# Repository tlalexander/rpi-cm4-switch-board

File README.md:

# RPi CM4 - Gigabit switch prototyping board

A raspberry pi cm4 board with integrated gigabit switch.

Two CM4s and three RJ45 Jacks each connected to a [Microchip KSZ9567](https://www.microchip.com/wwwproducts/en/KSZ9567#datasheet-toggle)

In the future I will make a board with four CM4 modules and one RJ45 on the
switch, but for now I am making this so I can test the switch on its own.

However this also makes for an interesting board in its own right, as two
wifi CM4 modules could make this an interesting router board.

## About

This project is maintained by [Taylor Alexander](http://tlalexander.com).

The Raspberry Pi CM4 is a product of [Raspberry Pi (Trading) Limited](https://www.raspberrypi.org/about/).

This Raspberry Pi CM4 switch board was forked from
[Alexander Rau's](https://rpi.loonix.ca) rpi-cm4-LiM-board:
https://github.com/l00nix/rpi-cm4-LiM-board

Alexander Rau forked the rpi-cm4-LiM-board board design from [Shawn Hymel](https://github.com/ShawnHymel/rpi-cm4-base-carrier).
Shawn has a two part youtube series on how to design a CM4 Carrier Board.

- [Part 1 - How to Make a Raspberry Pi Compute Module 4 Carrier Board in KiCad](https://www.youtube.com/watch?v=ypcPJC_umPQ)
- [Part 2 - How to Make a Raspberry Pi Compute Module 4 Carrier Board in KiCad](https://www.youtube.com/watch?v=ge6gYIENo8Q&t)

## License

Schematic and PCB layout files are licensed under the [CC BY 4.0](https://creativecommons.org/licenses/by/2.0/) license.

Individual components and footprints found in the CM4IO library are licensed as
per the Design Files license found [here](https://datasheets.raspberrypi.org/license.html).

THE DESIGN IS PROVIDED "AS IS" AND THE AUTHOR DISCLAIMS ALL WARRANTIES WITH
REGARD TO THIS DESIGN INCLUDING ALL IMPLIED WARRANTIES OF MERCHANTABILITY AND
FITNESS. IN NO EVENT SHALL THE AUTHOR BE LIABLE FOR ANY SPECIAL, DIRECT,
INDIRECT, OR CONSEQUENTIAL DAMAGES OR ANY DAMAGES WHATSOEVER RESULTING FROM
LOSS OF USE, DATA OR PROFITS, WHETHER IN AN ACTION OF CONTRACT, NEGLIGENCE
OR OTHER TORTIOUS ACTION, ARISING OUT OF OR IN CONNECTION WITH THE USE OR
PERFORMANCE OF THIS DESIGN.

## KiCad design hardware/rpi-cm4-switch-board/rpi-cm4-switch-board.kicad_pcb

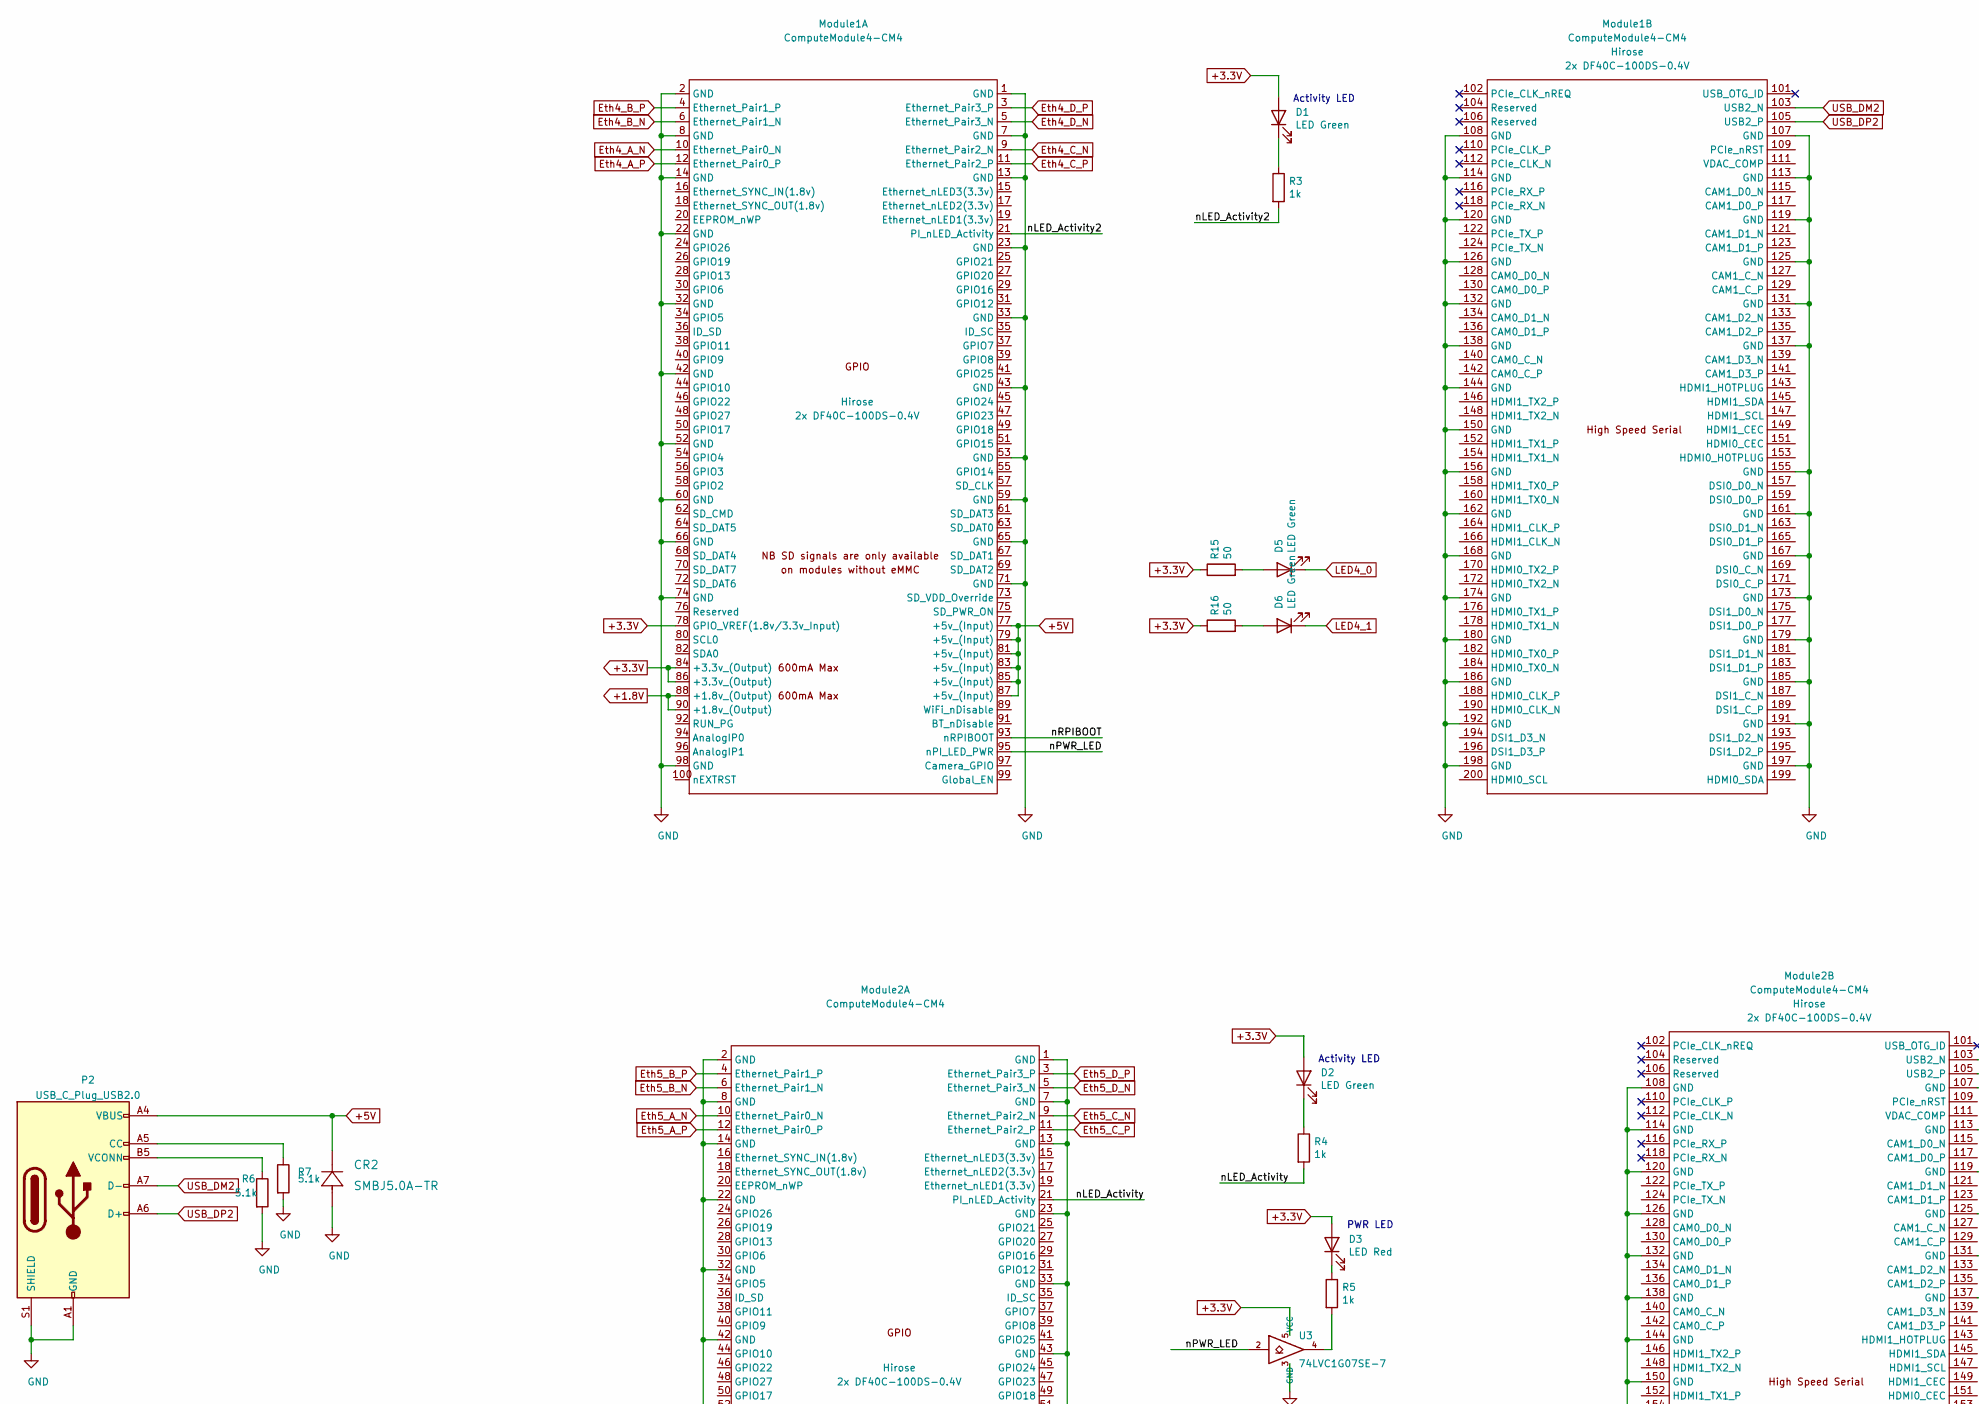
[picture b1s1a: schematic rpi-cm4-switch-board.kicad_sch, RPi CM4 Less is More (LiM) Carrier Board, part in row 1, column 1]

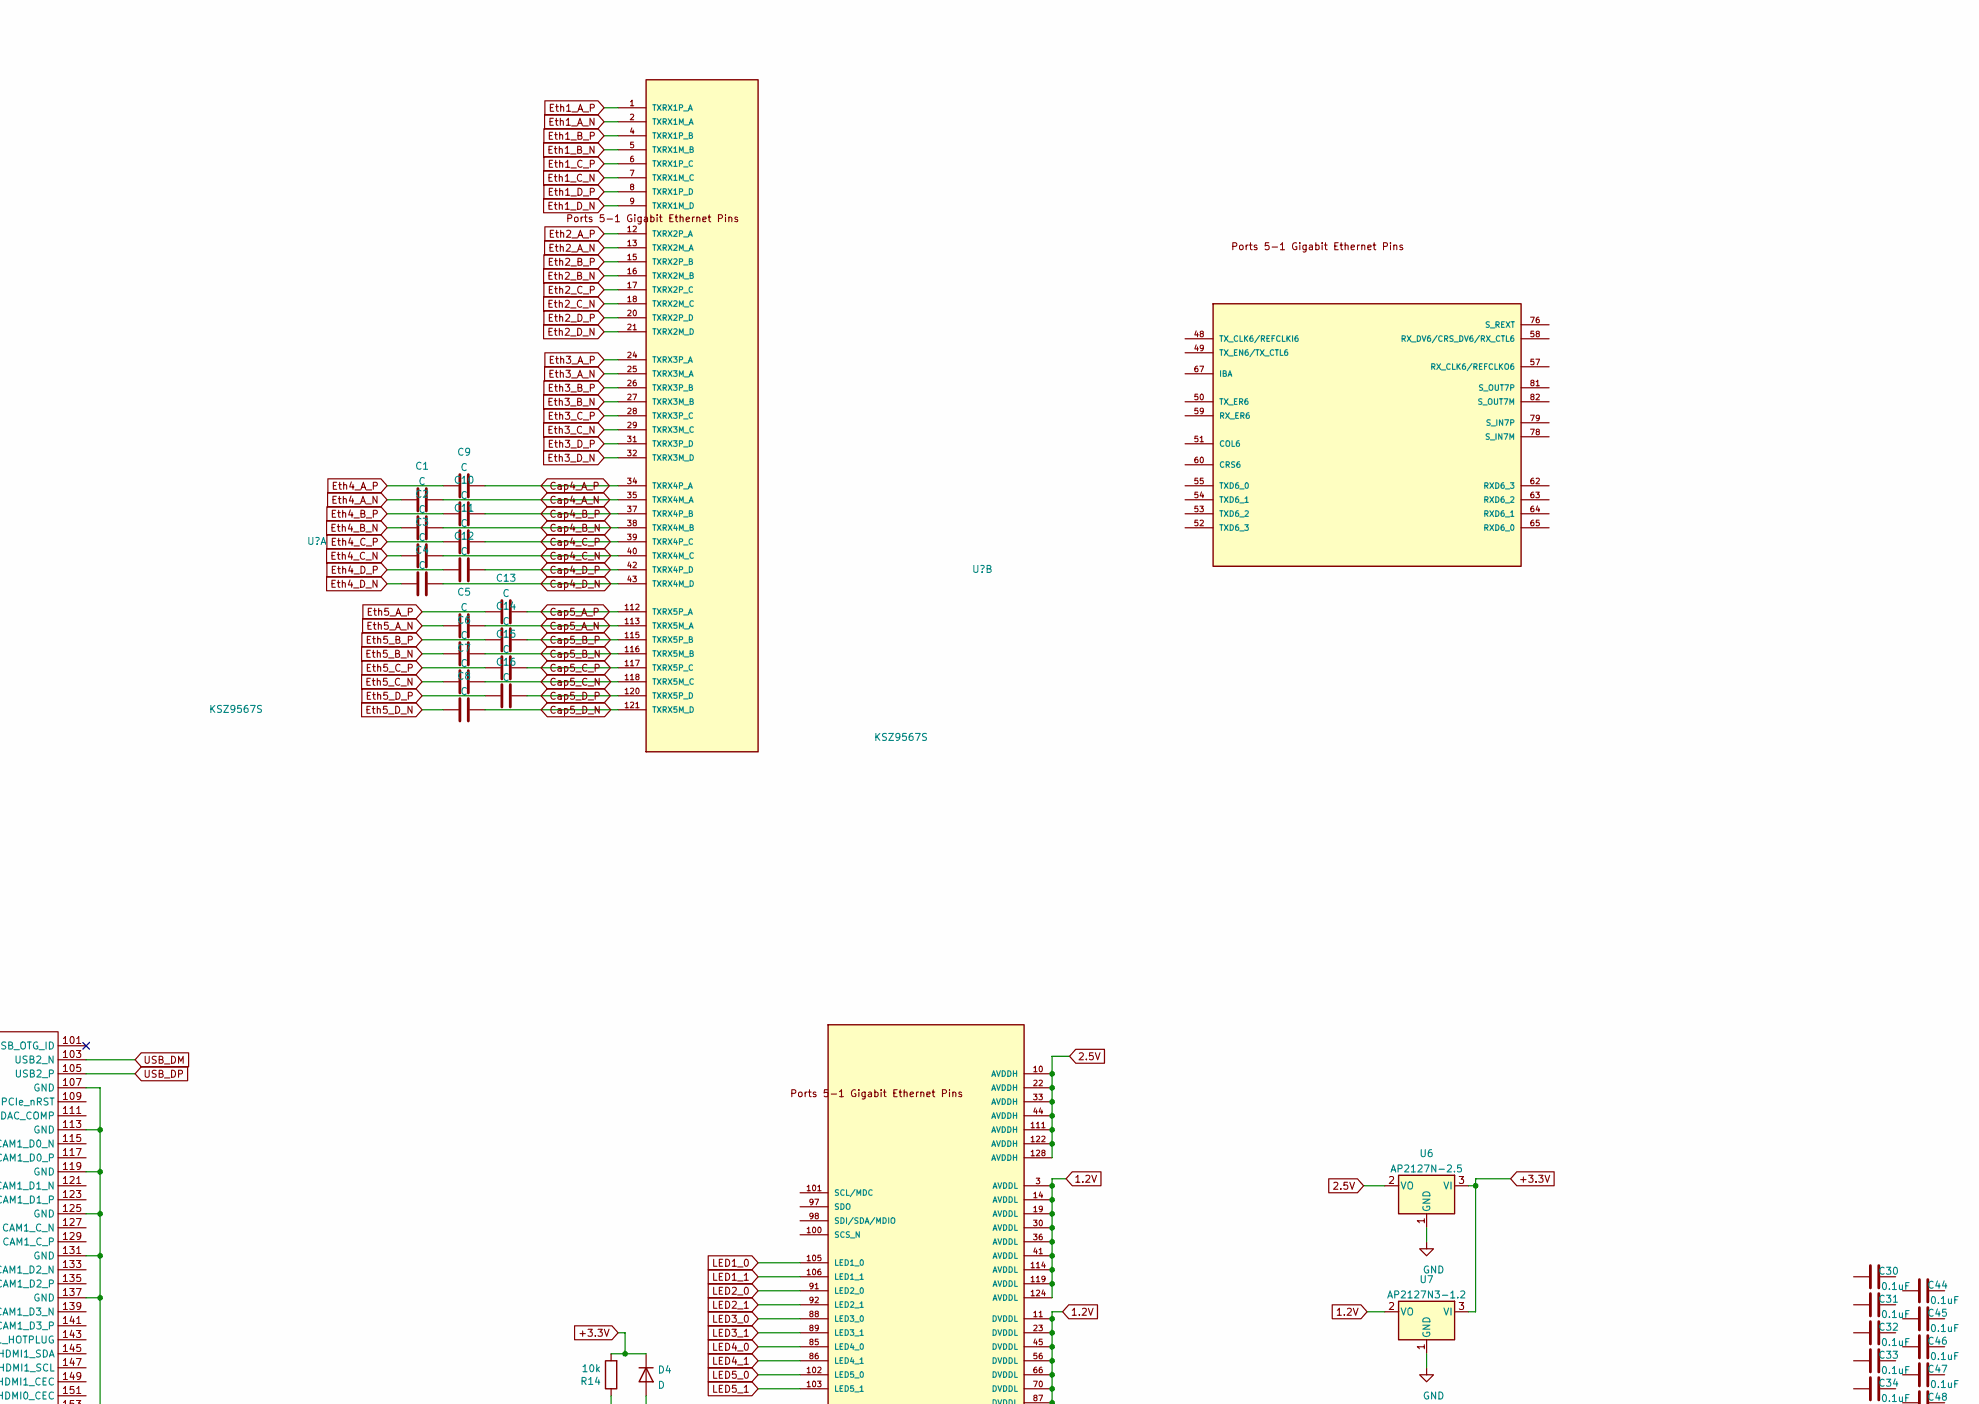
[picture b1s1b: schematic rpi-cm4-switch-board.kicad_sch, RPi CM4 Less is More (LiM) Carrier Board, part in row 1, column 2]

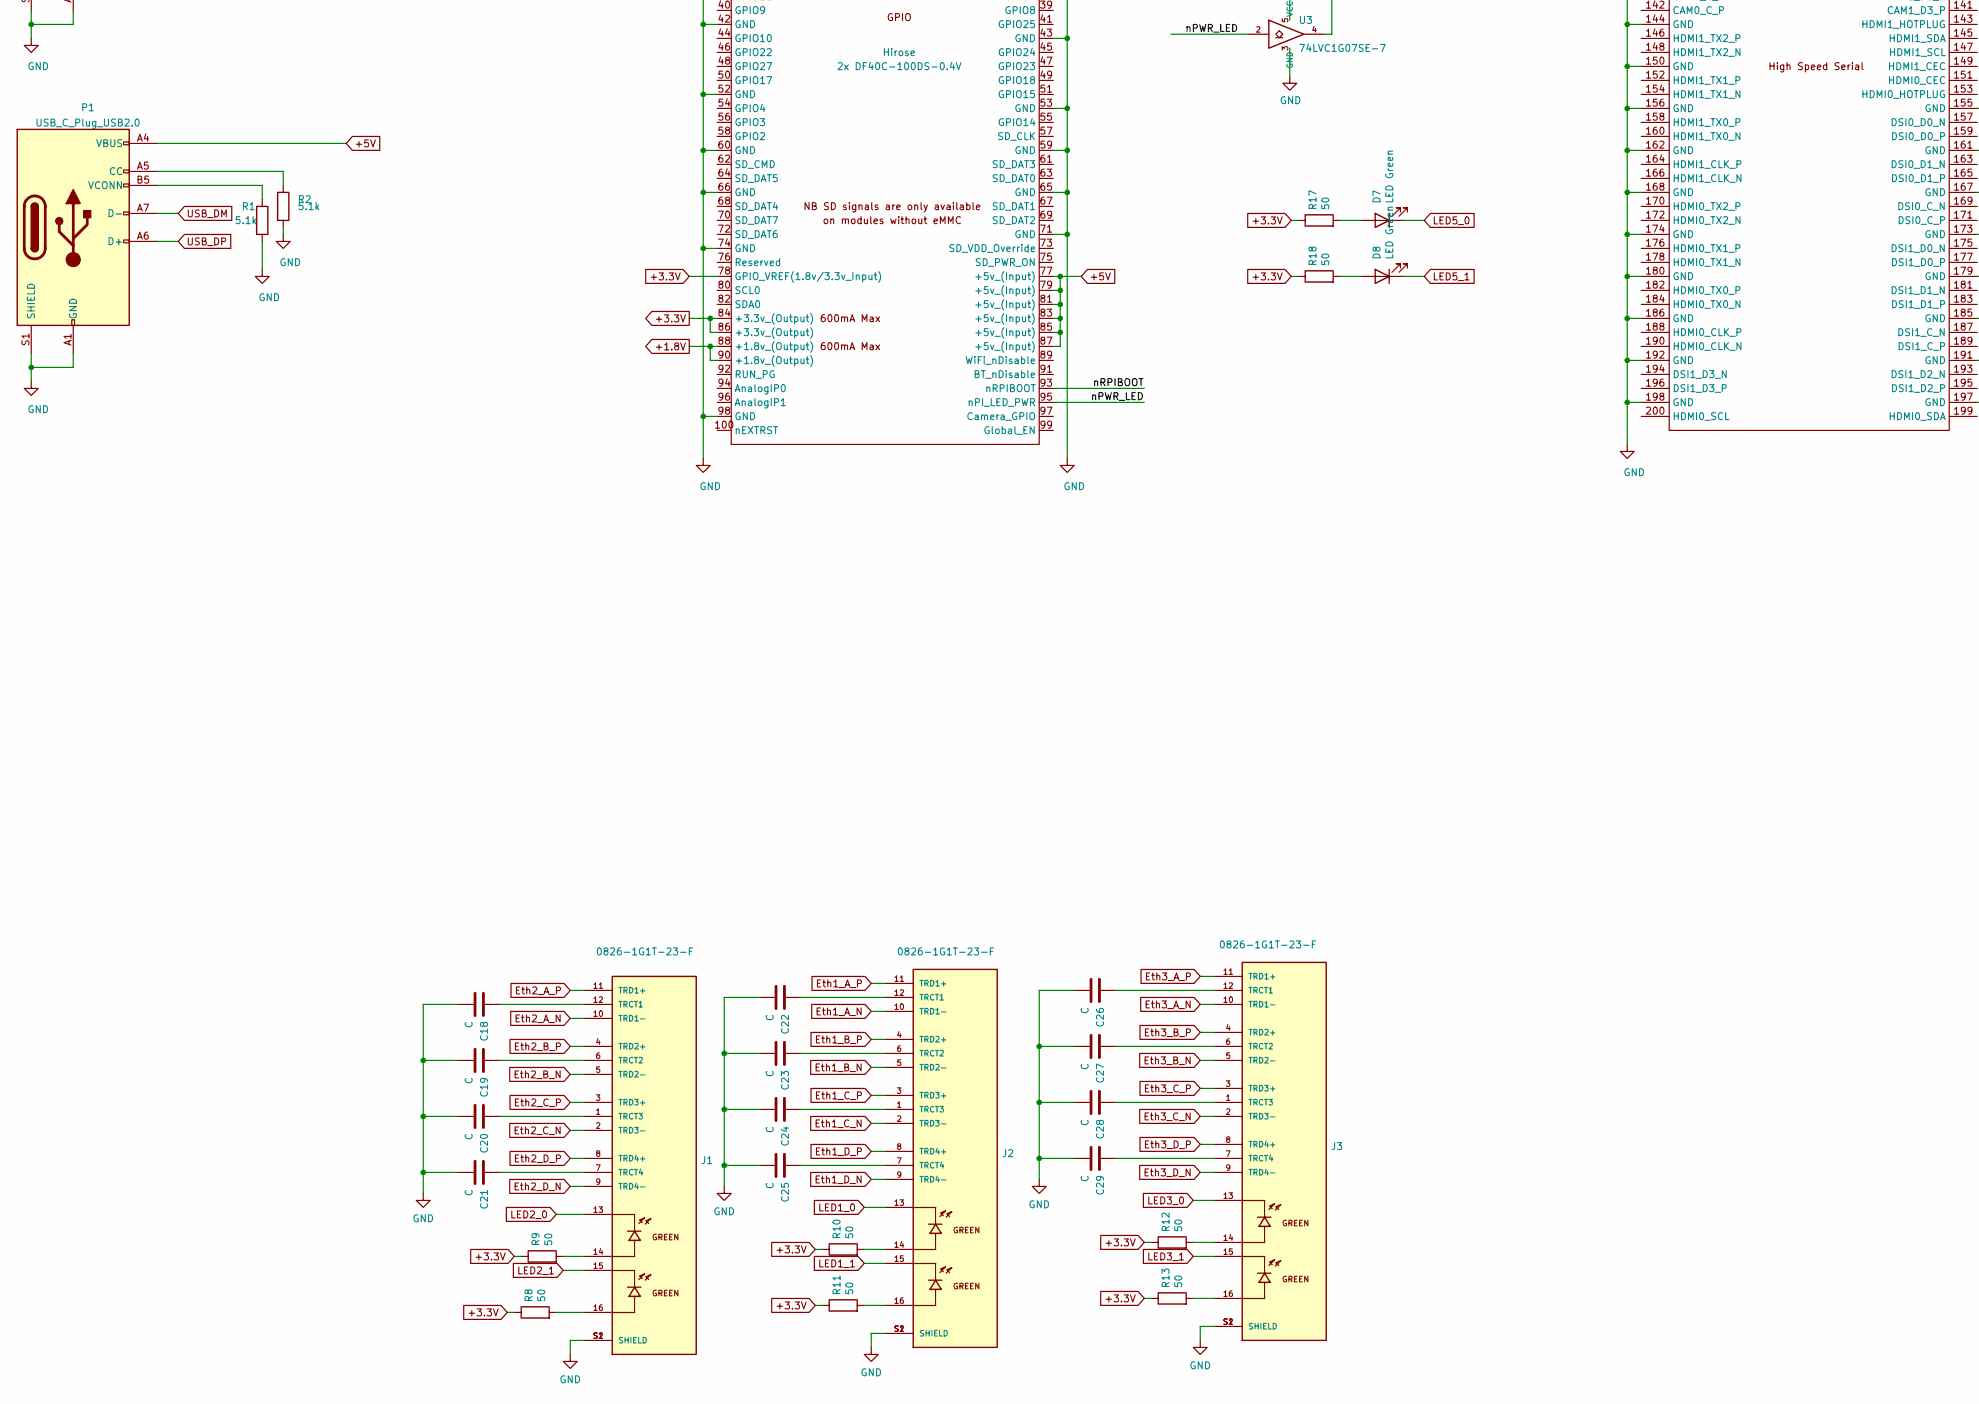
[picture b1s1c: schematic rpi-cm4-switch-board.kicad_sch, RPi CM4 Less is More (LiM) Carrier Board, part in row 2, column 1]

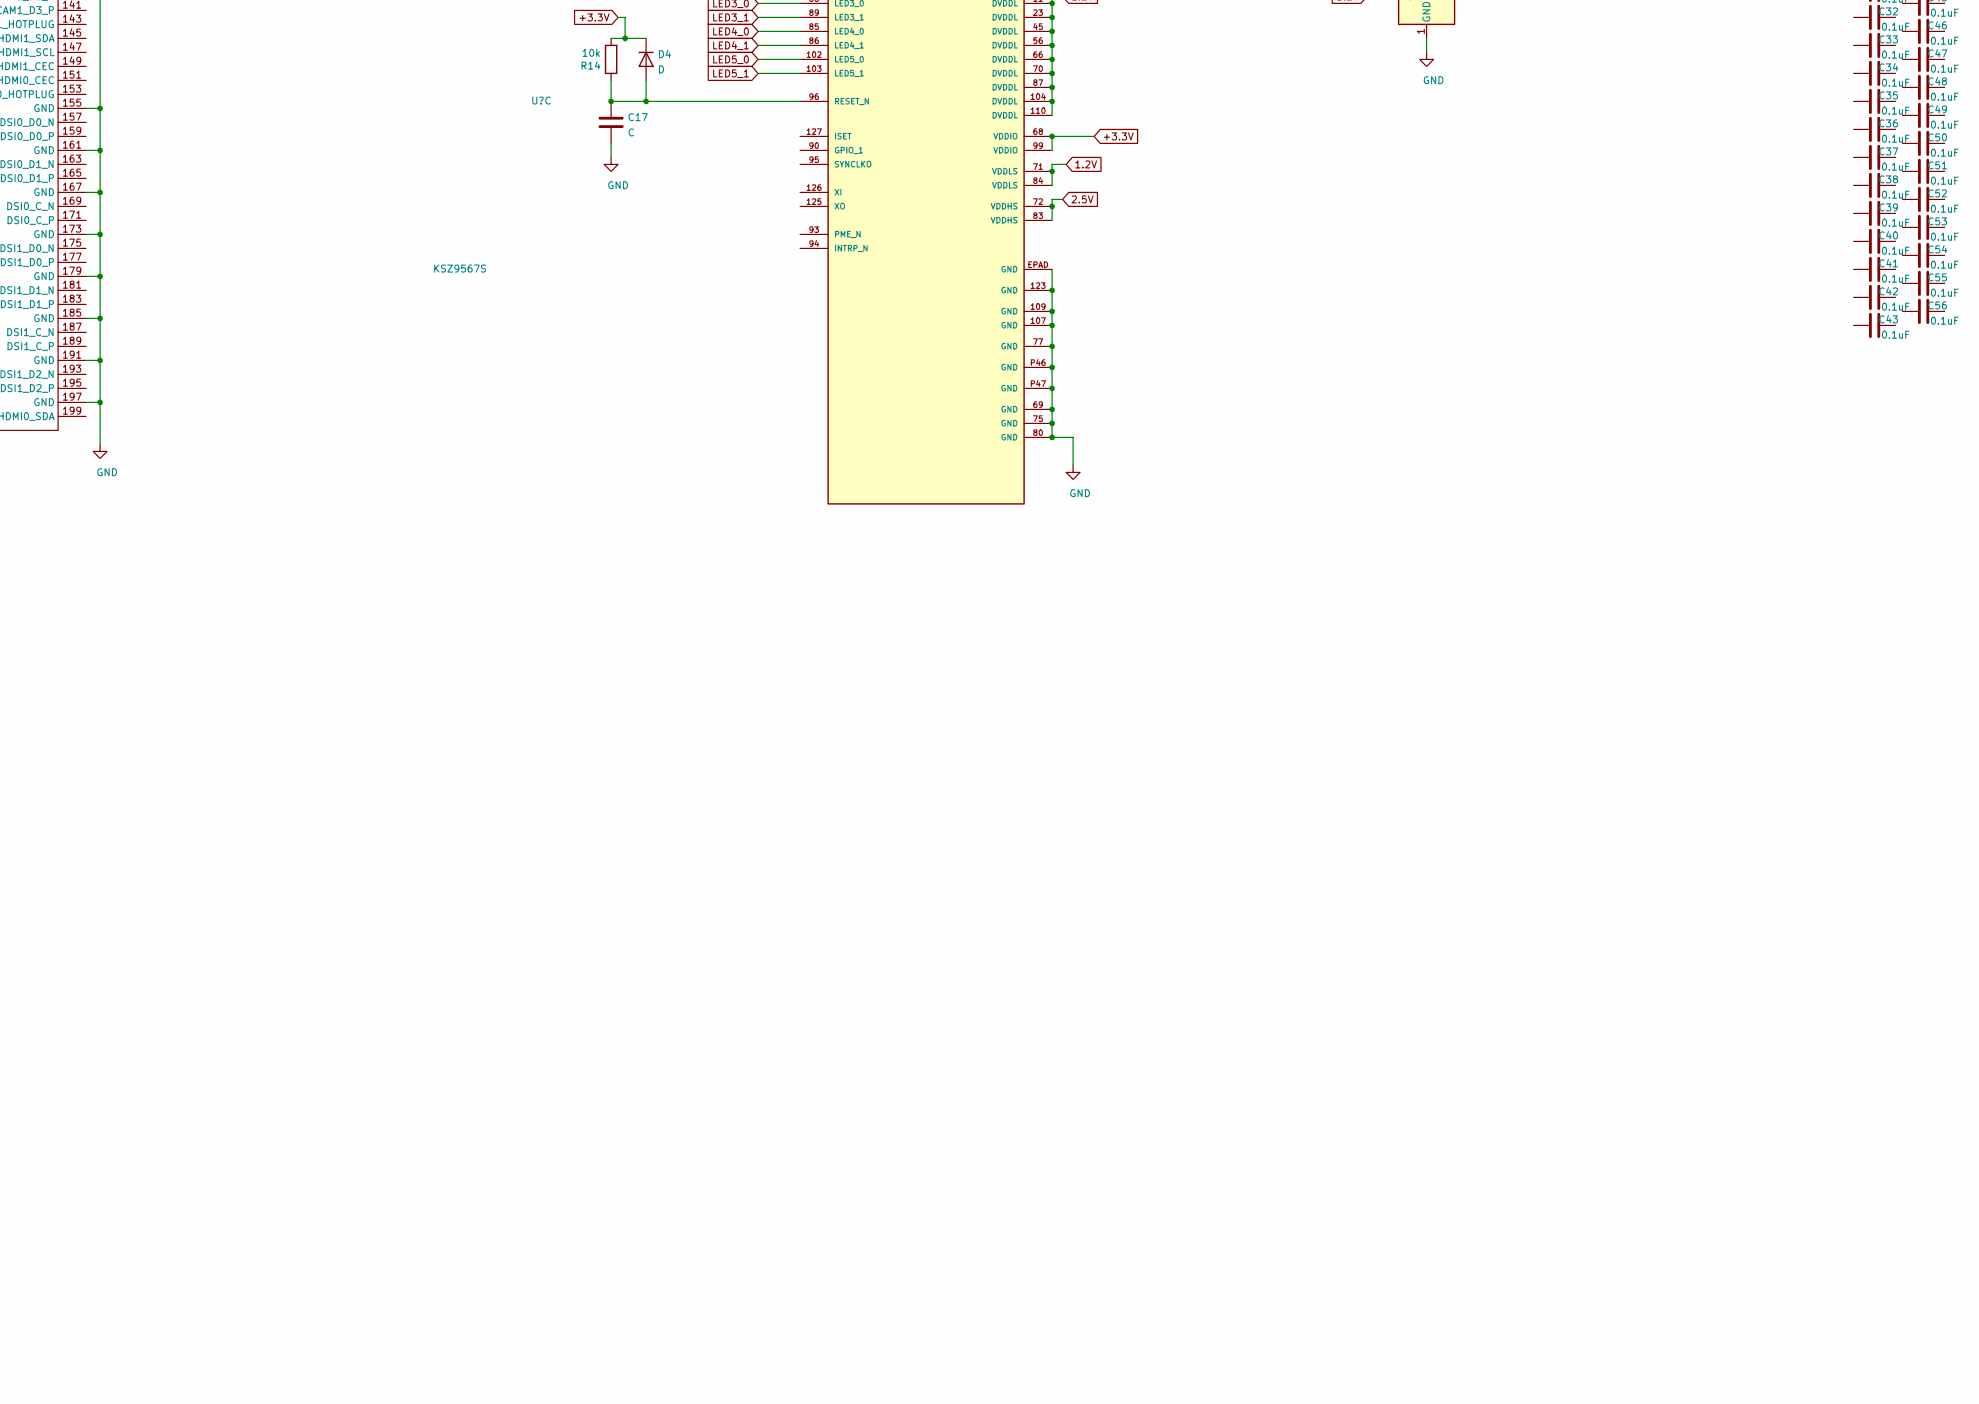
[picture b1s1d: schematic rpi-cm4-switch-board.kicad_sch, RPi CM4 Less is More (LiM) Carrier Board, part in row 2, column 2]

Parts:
C1, C2, C3, C4, C5, C6, C7, C8, C9, C10, C11, C12, C13, C14, C15, C16, C18, C19, C20, C21, C22, C23, C24, C25, C26, C27, C28, C29: C; C_0402_1005Metric
C17: C; C_0805_2012Metric
C30, C31, C32, C33, C34, C35, C36, C37, C38, C39, C40, C41, C42, C43, C44, C45, C46, C47, C48, C49, C50, C51, C52, C53, C54, C55, C56: 0.1uF; C_0402_1005Metric
CR2: SMBJ5.0A-TR; MPN SMBJ5.0A-TR; Digi-Key_PN 497-3144-1-ND
D1, D2, D5, D6, D7, D8: LED Green; LED_0603_1608Metric; Part Description Green 572nm LED Indication - Discrete 2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; Digi-Key_PN 160-1478-1-ND
D3: LED Red; LED_0603_1608Metric; Part Description Red 620nm LED Indication - Discrete 2.2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; Digi-Key_PN 160-1479-1-ND
D4: D; D_SOD-323
J1, J2, J3: 0826-1G1T-23-F; BEL_0826-1G1T-23-F
Module1, Module2: ComputeModule4-CM4; Raspberry-Pi-4-Compute-Module; MPN 2x DF40C-100DS-0.4V; Digi-Key_PN 2x H11615CT-ND
P1, P2: USB_C_Plug_USB2.0; USB_C_Receptacle_GCT_USB4085
R1, R2, R6, R7: 5.1k; R_0603_1608Metric; MPN RC0603FR-075K1L; Digi-Key_PN 311-5.10KHRCT-ND
R3, R4, R5: 1k; R_0603_1608Metric; MPN RC0603FR-071KL; Digi-Key_PN 311-1.00KHRCT-ND
R8, R9, R10, R11, R12, R13, R15, R16, R17, R18: 50; R_0603_1608Metric; MPN RC0603FR-071KL; Digi-Key_PN 311-1.00KHRCT-ND
R14: 10k; R_0603_1608Metric; MPN RC0603FR-071KL; Digi-Key_PN 311-1.00KHRCT-ND
U3: 74LVC1G07SE-7; SOT-353_SC-70-5; Part Description Buffer, Non-Inverting 1 Element 1 Bit p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; Digi-Key_PN 74LVC1G07SE-7DICT-ND
U6: AP2127N-2.5; SOT-23
U7: AP2127N3-1.2; TSOT-23

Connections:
1.2V: U7.2 (VO); also elsewhere on the board
2.5V: U6.2 (VO); also elsewhere on the board
+1.8V: Module1.88 (+1.8v_(Output)), Module1.90 (+1.8v_(Output)), Module2.88 (+1.8v_(Output)), Module2.90 (+1.8v_(Output))
+3.3V: D1.2 (A), D2.2 (A), D3.2 (A), D4.1 (K), Module1.78 (GPIO_VREF(1.8v/3.3v_Input)), Module1.84 (+3.3v_(Output)), Module1.86 (+3.3v_(Output)), Module2.78 (GPIO_VREF(1.8v/3.3v_Input)), Module2.84 (+3.3v_(Output)), Module2.86 (+3.3v_(Output)), R8.1, R9.1, R10.1, R11.1, R12.1, R13.1, R14.2, R15.1, R16.1, R17.1, R18.1, U3.5 (VCC), U6.3 (VI), U7.3 (VI); also elsewhere on the board
+5V: CR2.1, Module1.77 (+5v_(Input)), Module1.79 (+5v_(Input)), Module1.81 (+5v_(Input)), Module1.83 (+5v_(Input)), Module1.85 (+5v_(Input)), Module1.87 (+5v_(Input)), Module2.77 (+5v_(Input)), Module2.79 (+5v_(Input)), Module2.81 (+5v_(Input)), Module2.83 (+5v_(Input)), Module2.85 (+5v_(Input)), Module2.87 (+5v_(Input)), P1.A4 (VBUS), P1.A9 (VBUS), P1.B4 (VBUS), P1.B9 (VBUS), P2.A4 (VBUS), P2.A9 (VBUS), P2.B4 (VBUS), P2.B9 (VBUS)
/nLED_Activity: Module2.21 (PI_nLED_Activity), R4.2
/nLED_Activity2: Module1.21 (PI_nLED_Activity), R3.2
/nPWR_LED: Module1.95 (nPI_LED_PWR), Module2.95 (nPI_LED_PWR), U3.2
/nRPIBOOT: Module1.93 (nRPIBOOT), Module2.93 (nRPIBOOT)
Cap4_A_N: C1.2; also elsewhere on the board
Cap4_A_P: C9.2; also elsewhere on the board
Cap4_B_N: C2.2; also elsewhere on the board
Cap4_B_P: C10.2; also elsewhere on the board
Cap4_C_N: C3.2; also elsewhere on the board
Cap4_C_P: C11.2; also elsewhere on the board
Cap4_D_N: C4.2; also elsewhere on the board
Cap4_D_P: C12.2; also elsewhere on the board
Cap5_A_N: C5.2; also elsewhere on the board
Cap5_A_P: C13.2; also elsewhere on the board
Cap5_B_N: C6.2; also elsewhere on the board
Cap5_B_P: C14.2; also elsewhere on the board
Cap5_C_N: C7.2; also elsewhere on the board
Cap5_C_P: C15.2; also elsewhere on the board
Cap5_D_N: C8.2; also elsewhere on the board
Cap5_D_P: C16.2; also elsewhere on the board
Eth1_A_N: J2.10 (TRD1-); also elsewhere on the board
Eth1_A_P: J2.11 (TRD1+); also elsewhere on the board
Eth1_B_N: J2.5 (TRD2-); also elsewhere on the board
Eth1_B_P: J2.4 (TRD2+); also elsewhere on the board
Eth1_C_N: J2.2 (TRD3-); also elsewhere on the board
Eth1_C_P: J2.3 (TRD3+); also elsewhere on the board
Eth1_D_N: J2.9 (TRD4-); also elsewhere on the board
Eth1_D_P: J2.8 (TRD4+); also elsewhere on the board
Eth2_A_N: J1.10 (TRD1-); also elsewhere on the board
Eth2_A_P: J1.11 (TRD1+); also elsewhere on the board
Eth2_B_N: J1.5 (TRD2-); also elsewhere on the board
Eth2_B_P: J1.4 (TRD2+); also elsewhere on the board
Eth2_C_N: J1.2 (TRD3-); also elsewhere on the board
Eth2_C_P: J1.3 (TRD3+); also elsewhere on the board
Eth2_D_N: J1.9 (TRD4-); also elsewhere on the board
Eth2_D_P: J1.8 (TRD4+); also elsewhere on the board
Eth3_A_N: J3.10 (TRD1-); also elsewhere on the board
Eth3_A_P: J3.11 (TRD1+); also elsewhere on the board
Eth3_B_N: J3.5 (TRD2-); also elsewhere on the board
Eth3_B_P: J3.4 (TRD2+); also elsewhere on the board
Eth3_C_N: J3.2 (TRD3-); also elsewhere on the board
Eth3_C_P: J3.3 (TRD3+); also elsewhere on the board
Eth3_D_N: J3.9 (TRD4-); also elsewhere on the board
Eth3_D_P: J3.8 (TRD4+); also elsewhere on the board
Eth4_A_N: C1.1, Module1.10 (Ethernet_Pair0_N)
Eth4_A_P: C9.1, Module1.12 (Ethernet_Pair0_P)
Eth4_B_N: C2.1, Module1.6 (Ethernet_Pair1_N)
Eth4_B_P: C10.1, Module1.4 (Ethernet_Pair1_P)
Eth4_C_N: C3.1, Module1.9 (Ethernet_Pair2_N)
Eth4_C_P: C11.1, Module1.11 (Ethernet_Pair2_P)
Eth4_D_N: C4.1, Module1.5 (Ethernet_Pair3_N)
Eth4_D_P: C12.1, Module1.3 (Ethernet_Pair3_P)
Eth5_A_N: C5.1, Module2.10 (Ethernet_Pair0_N)
Eth5_A_P: C13.1, Module2.12 (Ethernet_Pair0_P)
Eth5_B_N: C6.1, Module2.6 (Ethernet_Pair1_N)
Eth5_B_P: C14.1, Module2.4 (Ethernet_Pair1_P)
Eth5_C_N: C7.1, Module2.9 (Ethernet_Pair2_N)
Eth5_C_P: C15.1, Module2.11 (Ethernet_Pair2_P)
Eth5_D_N: C8.1, Module2.5 (Ethernet_Pair3_N)
Eth5_D_P: C16.1, Module2.3 (Ethernet_Pair3_P)
GND: C17.2, C18.2, C19.2, C20.2, C21.2, C22.2, C23.2, C24.2, C25.2, C26.2, C27.2, C28.2, C29.2, CR2.2, J1.S1 (SHIELD), J1.S2 (SHIELD), J2.S1 (SHIELD), J2.S2 (SHIELD), J3.S1 (SHIELD), J3.S2 (SHIELD), Module1.1 (GND), Module1.2 (GND), Module1.7 (GND), Module1.8 (GND), Module1.13 (GND), Module1.14 (GND), Module1.22 (GND), Module1.23 (GND), Module1.32 (GND), Module1.33 (GND), Module1.42 (GND), Module1.43 (GND), Module1.52 (GND), Module1.53 (GND), Module1.59 (GND), Module1.60 (GND), Module1.65 (GND), Module1.66 (GND), Module1.71 (GND), Module1.74 (GND), Module1.98 (GND), Module1.107 (GND), Module1.108 (GND), Module1.113 (GND), Module1.114 (GND), Module1.119 (GND), Module1.120 (GND), Module1.125 (GND), Module1.126 (GND), Module1.131 (GND), Module1.132 (GND), Module1.137 (GND), Module1.138 (GND), Module1.144 (GND), Module1.150 (GND), Module1.155 (GND), Module1.156 (GND), Module1.161 (GND), Module1.162 (GND), Module1.167 (GND), Module1.168 (GND), Module1.173 (GND), Module1.174 (GND), Module1.179 (GND), Module1.180 (GND), Module1.185 (GND), Module1.186 (GND), Module1.191 (GND), Module1.192 (GND), Module1.197 (GND), Module1.198 (GND), Module2.1 (GND), Module2.2 (GND), Module2.7 (GND), Module2.8 (GND), Module2.13 (GND), Module2.14 (GND), Module2.22 (GND), Module2.23 (GND), Module2.32 (GND), Module2.33 (GND), Module2.42 (GND), Module2.43 (GND), Module2.52 (GND), Module2.53 (GND), Module2.59 (GND), Module2.60 (GND), Module2.65 (GND), Module2.66 (GND), Module2.71 (GND), Module2.74 (GND), Module2.98 (GND), Module2.107 (GND), Module2.108 (GND), Module2.113 (GND), Module2.114 (GND), Module2.119 (GND), Module2.120 (GND), Module2.125 (GND), Module2.126 (GND), Module2.131 (GND), Module2.132 (GND), Module2.137 (GND), Module2.138 (GND), Module2.144 (GND), Module2.150 (GND), Module2.155 (GND), Module2.156 (GND), Module2.161 (GND), Module2.162 (GND), Module2.167 (GND), Module2.168 (GND), Module2.173 (GND), Module2.174 (GND), Module2.179 (GND), Module2.180 (GND), Module2.185 (GND), Module2.186 (GND), Module2.191 (GND), Module2.192 (GND), Module2.197 (GND), Module2.198 (GND), P1.A1 (GND), P1.A12 (GND), P1.B1 (GND), P1.B12 (GND), P1.S1 (SHIELD), P2.A1 (GND), P2.A12 (GND), P2.B1 (GND), P2.B12 (GND), P2.S1 (SHIELD), R1.2, R2.2, R6.2, R7.2, U3.3 (GND), U6.1 (GND), U7.1 (GND); also elsewhere on the board
LED1_0: J2.13; also elsewhere on the board
LED1_1: J2.15; also elsewhere on the board
LED2_0: J1.13; also elsewhere on the board
LED2_1: J1.15; also elsewhere on the board
LED3_0: J3.13; also elsewhere on the board
LED3_1: J3.15; also elsewhere on the board
LED4_0: D5.1 (K); also elsewhere on the board
LED4_1: D6.1 (K); also elsewhere on the board
LED5_0: D7.1 (K); also elsewhere on the board
LED5_1: D8.1 (K); also elsewhere on the board
unnamed 76: C17.1, D4.2 (A), R14.1; also elsewhere on the board
unnamed: C18.1, J1.12 (TRCT1)
unnamed: C19.1, J1.6 (TRCT2)
unnamed: C20.1, J1.1 (TRCT3)
unnamed: C21.1, J1.7 (TRCT4)
unnamed: C22.1, J2.12 (TRCT1)
unnamed: C23.1, J2.6 (TRCT2)
unnamed: C24.1, J2.1 (TRCT3)
unnamed: C25.1, J2.7 (TRCT4)
unnamed: C26.1, J3.12 (TRCT1)
unnamed: C27.1, J3.6 (TRCT2)
unnamed: C28.1, J3.1 (TRCT3)
unnamed: C29.1, J3.7 (TRCT4)
unnamed: D1.1 (K), R3.1
unnamed: D2.1 (K), R4.1
unnamed: D3.1 (K), R5.1
unnamed: D5.2 (A), R15.2
unnamed: D6.2 (A), R16.2
unnamed: D7.2 (A), R17.2
unnamed: D8.2 (A), R18.2
unnamed: J1.14, R9.2
unnamed: J1.16, R8.2
unnamed: J2.14, R10.2
unnamed: J2.16, R11.2
unnamed: J3.14, R12.2
unnamed: J3.16, R13.2
unnamed: P1.A5 (CC), R2.1
unnamed: P1.B5 (VCONN), R1.1
unnamed: P2.A5 (CC), R7.1
unnamed: P2.B5 (VCONN), R6.1
unnamed: R5.2, U3.4
USB_DM: Module2.103 (USB2_N), P1.A7 (D-)
USB_DM2: Module1.103 (USB2_N), P2.A7 (D-)
USB_DP: Module2.105 (USB2_P), P1.A6 (D+)
USB_DP2: Module1.105 (USB2_P), P2.A6 (D+)

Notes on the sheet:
Activity LED
PWR LED

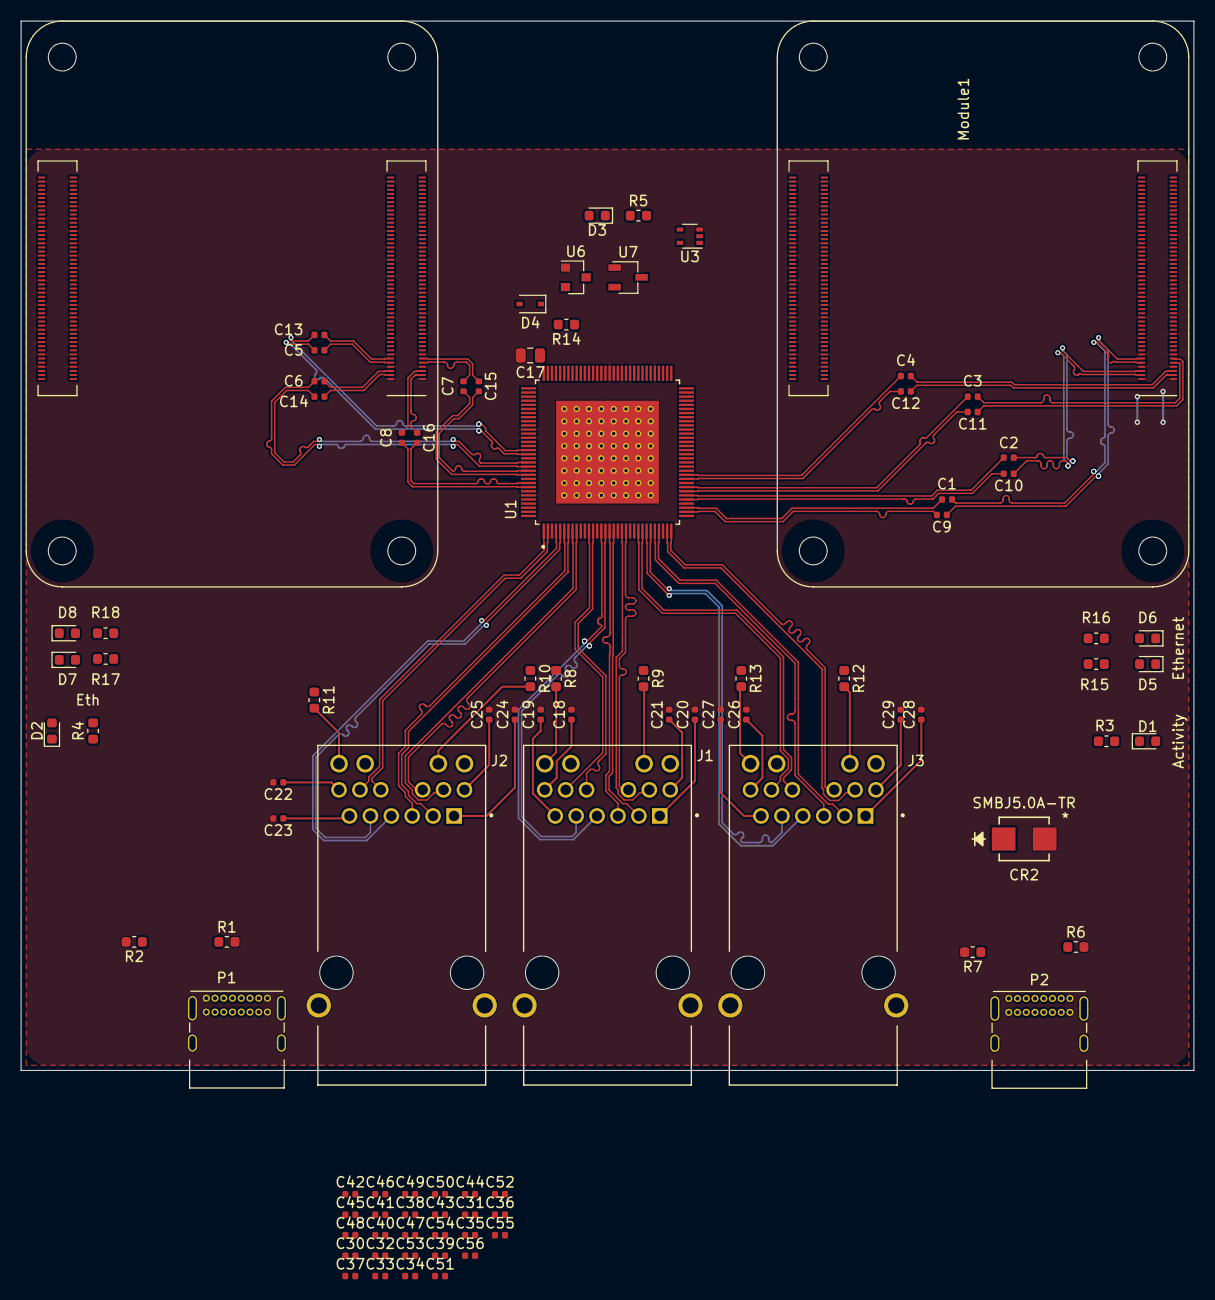
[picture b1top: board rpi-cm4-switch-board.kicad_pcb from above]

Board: 2 copper layers, 114.0 x 102.0 mm, 94 parts (0 on the bottom side), 111 nets.

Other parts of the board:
U1: KSZ9567S; QFP40P1600X1600X120-129N

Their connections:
1.2V: U1.3 (AVDDL), U1.11 (DVDDL), U1.14 (AVDDL), U1.19 (AVDDL), U1.23 (DVDDL), U1.30 (AVDDL), U1.36 (AVDDL), U1.41 (AVDDL), U1.45 (DVDDL), U1.56 (DVDDL), U1.66 (DVDDL), U1.70 (DVDDL), U1.71 (VDDLS), U1.84 (VDDLS), U1.87 (DVDDL), U1.104 (DVDDL), U1.110 (DVDDL), U1.114 (AVDDL), U1.119 (AVDDL), U1.124 (AVDDL); also elsewhere on the board
2.5V: U1.10 (AVDDH), U1.22 (AVDDH), U1.33 (AVDDH), U1.44 (AVDDH), U1.72 (VDDHS), U1.83 (VDDHS), U1.111 (AVDDH), U1.122 (AVDDH), U1.128 (AVDDH); also elsewhere on the board
+3.3V: U1.68 (VDDIO), U1.99 (VDDIO); also elsewhere on the board
Cap4_A_N: U1.35 (TXRX4M_A); also elsewhere on the board
Cap4_A_P: U1.34 (TXRX4P_A); also elsewhere on the board
Cap4_B_N: U1.38 (TXRX4M_B); also elsewhere on the board
Cap4_B_P: U1.37 (TXRX4P_B); also elsewhere on the board
Cap4_C_N: U1.40 (TXRX4M_C); also elsewhere on the board
Cap4_C_P: U1.39 (TXRX4P_C); also elsewhere on the board
Cap4_D_N: U1.43 (TXRX4M_D); also elsewhere on the board
Cap4_D_P: U1.42 (TXRX4P_D); also elsewhere on the board
Cap5_A_N: U1.113 (TXRX5M_A); also elsewhere on the board
Cap5_A_P: U1.112 (TXRX5P_A); also elsewhere on the board
Cap5_B_N: U1.116 (TXRX5M_B); also elsewhere on the board
Cap5_B_P: U1.115 (TXRX5P_B); also elsewhere on the board
Cap5_C_N: U1.118 (TXRX5M_C); also elsewhere on the board
Cap5_C_P: U1.117 (TXRX5P_C); also elsewhere on the board
Cap5_D_N: U1.121 (TXRX5M_D); also elsewhere on the board
Cap5_D_P: U1.120 (TXRX5P_D); also elsewhere on the board
Eth1_A_N: U1.2 (TXRX1M_A); also elsewhere on the board
Eth1_A_P: U1.1 (TXRX1P_A); also elsewhere on the board
Eth1_B_N: U1.5 (TXRX1M_B); also elsewhere on the board
Eth1_B_P: U1.4 (TXRX1P_B); also elsewhere on the board
Eth1_C_N: U1.7 (TXRX1M_C); also elsewhere on the board
Eth1_C_P: U1.6 (TXRX1P_C); also elsewhere on the board
Eth1_D_N: U1.9 (TXRX1M_D); also elsewhere on the board
Eth1_D_P: U1.8 (TXRX1P_D); also elsewhere on the board
Eth2_A_N: U1.13 (TXRX2M_A); also elsewhere on the board
Eth2_A_P: U1.12 (TXRX2P_A); also elsewhere on the board
Eth2_B_N: U1.16 (TXRX2M_B); also elsewhere on the board
Eth2_B_P: U1.15 (TXRX2P_B); also elsewhere on the board
Eth2_C_N: U1.18 (TXRX2M_C); also elsewhere on the board
Eth2_C_P: U1.17 (TXRX2P_C); also elsewhere on the board
Eth2_D_N: U1.21 (TXRX2M_D); also elsewhere on the board
Eth2_D_P: U1.20 (TXRX2P_D); also elsewhere on the board
Eth3_A_N: U1.25 (TXRX3M_A); also elsewhere on the board
Eth3_A_P: U1.24 (TXRX3P_A); also elsewhere on the board
Eth3_B_N: U1.27 (TXRX3M_B); also elsewhere on the board
Eth3_B_P: U1.26 (TXRX3P_B); also elsewhere on the board
Eth3_C_N: U1.29 (TXRX3M_C); also elsewhere on the board
Eth3_C_P: U1.28 (TXRX3P_C); also elsewhere on the board
Eth3_D_N: U1.32 (TXRX3M_D); also elsewhere on the board
Eth3_D_P: U1.31 (TXRX3P_D); also elsewhere on the board
GND: U1.69 (GND), U1.75 (GND), U1.77 (GND), U1.80 (GND), U1.107 (GND), U1.109 (GND), U1.123 (GND), U1.EPAD (GND), U1.P46 (GND), U1.P47 (GND); also elsewhere on the board
LED1_0: U1.105 (LED1_0); also elsewhere on the board
LED1_1: U1.106 (LED1_1); also elsewhere on the board
LED2_0: U1.91 (LED2_0); also elsewhere on the board
LED2_1: U1.92 (LED2_1); also elsewhere on the board
LED3_0: U1.88 (LED3_0); also elsewhere on the board
LED3_1: U1.89 (LED3_1); also elsewhere on the board
LED4_0: U1.85 (LED4_0); also elsewhere on the board
LED4_1: U1.86 (LED4_1); also elsewhere on the board
LED5_0: U1.102 (LED5_0); also elsewhere on the board
LED5_1: U1.103 (LED5_1); also elsewhere on the board
unnamed 76: U1.96 (RESET_N); also elsewhere on the board

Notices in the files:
hardware/rpi-cm4-LiM-board/rpi-cm4-LiM-board.kicad_pcb:
creativecommons.org/licenses/by/4.0
License: CC BY-SA 4.0
parts and their libraries:
Copyright 2016 Accelerated Designs. All rights reserved.
